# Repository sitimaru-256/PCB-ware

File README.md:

# PCB-ware
"classD_amp" CH224KのVDDとGND間に1uFのキャパシタを追加してください。元の回路のままだと動きません。

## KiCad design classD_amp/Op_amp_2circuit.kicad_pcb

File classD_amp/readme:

CH224KのVDDとGND間に1uFのキャパシタを追加してください。元の回路のままだと動きません。

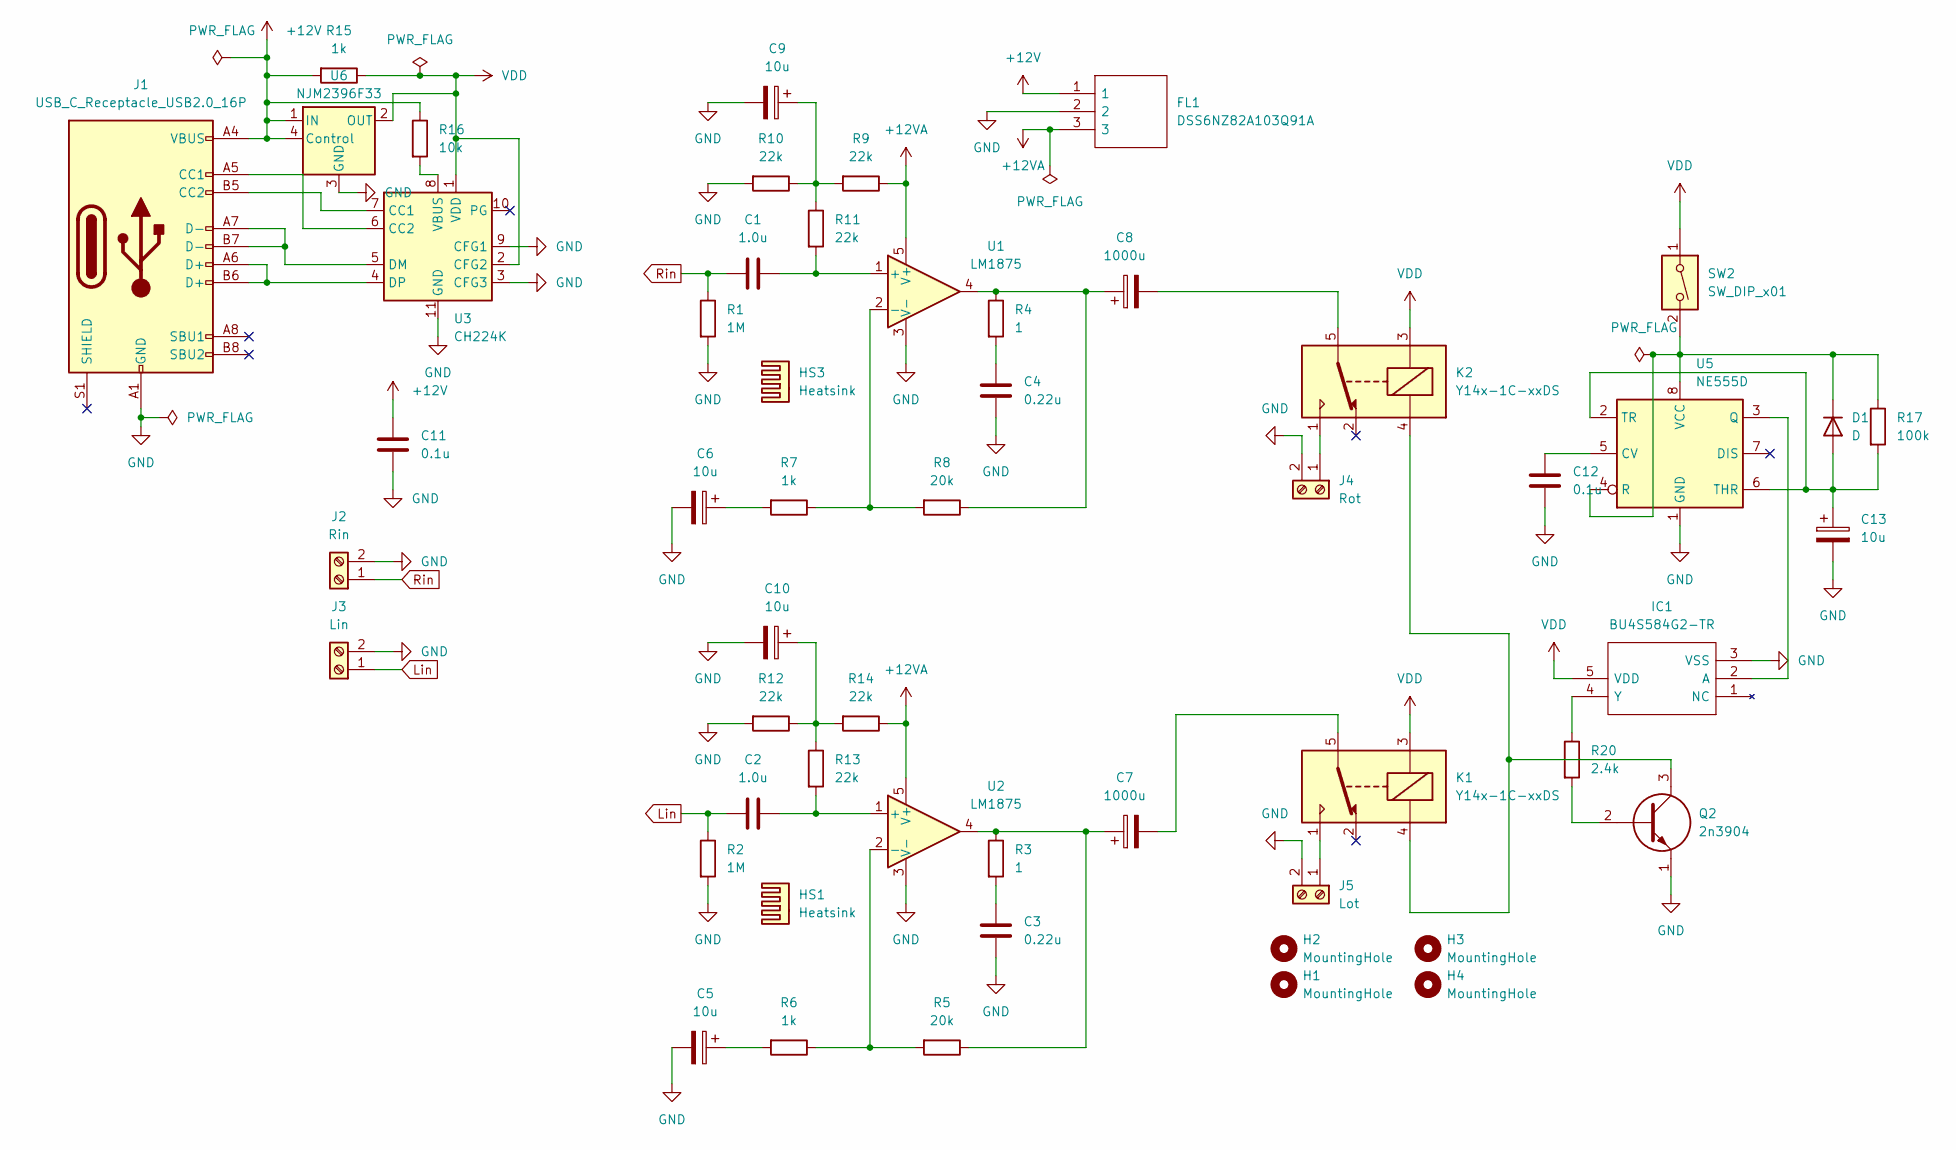
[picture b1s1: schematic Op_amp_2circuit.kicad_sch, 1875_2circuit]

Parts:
C1, C2: 1.0u; C_Rect_L7.0mm_W2.5mm_P5.00mm
C3, C4: 0.22u; C_Rect_L7.0mm_W2.5mm_P5.00mm
C5, C6, C9, C10, C13: 10u; C_Radial_D5.0mm_H11.0mm_P2.00mm
C7, C8: 1000u; C_Radial_D10.0mm_H16.0mm_P5.00mm
C11, C12: 0.1u; C_Rect_L7.0mm_W2.5mm_P5.00mm
D1: D; D_A-405_P7.62mm_Horizontal
FL1: DSS6NZ82A103Q91A; Manufacturer_Part_Number DSS6NZ82A103Q91A
H1, H2, H3, H4: MountingHole; MountingHole_3.2mm_M3
HS1, HS3: Heatsink; Heatsink_54x15x50mm_2xFixationM3
IC1: BU4S584G2-TR; SOT95P280X125-5N; Manufacturer_Part_Number BU4S584G2-TR
J1: USB_C_Receptacle_USB2.0_16P; USB_C_Receptacle_GCT_USB4105-xx-A_16P_TopMnt_Horizontal
J2: Rin; TerminalBlock_Altech_AK300-2_P5.00mm
J3: Lin; TerminalBlock_Altech_AK300-2_P5.00mm
J4: Rot; TerminalBlock_Altech_AK300-2_P5.00mm
J5: Lot; TerminalBlock_Altech_AK300-2_P5.00mm
K1, K2: Y14x-1C-xxDS; 946H-1C-3D
Q2: 2n3904; TS1107A1AP; Manufacturer_Part_Number 2n3904
R1, R2: 1M; R_Axial_DIN0207_L6.3mm_D2.5mm_P7.62mm_Horizontal
R3, R4: 1; R_Axial_DIN0207_L6.3mm_D2.5mm_P7.62mm_Horizontal
R5, R8: 20k; R_Axial_DIN0207_L6.3mm_D2.5mm_P7.62mm_Horizontal
R6, R7, R15: 1k; R_Axial_DIN0207_L6.3mm_D2.5mm_P7.62mm_Horizontal
R9, R10, R11, R12, R13, R14: 22k; R_Axial_DIN0207_L6.3mm_D2.5mm_P7.62mm_Horizontal
R16: 10k; R_Axial_DIN0207_L6.3mm_D2.5mm_P7.62mm_Horizontal
R17: 100k; R_Axial_DIN0207_L6.3mm_D2.5mm_P7.62mm_Horizontal
R20: 2.4k; R_Axial_DIN0207_L6.3mm_D2.5mm_P7.62mm_Horizontal
SW2: SW_DIP_x01; PinHeader_1x02_P2.54mm_Vertical
U1, U2: LM1875; TO-220-5_P3.4x3.7mm_StaggerOdd_Lead3.8mm_Vertical
U3: CH224K; SSOP-10-1EP_3.9x4.9mm_P1mm_EP2.1x3.3mm
U5: NE555D; SOIC-8_3.9x4.9mm_P1.27mm
U6: NJM2396F33; TO-220-4_Vertical

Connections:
+12V: C11.1, FL1.1, J1.A4 (VBUS), J1.A9 (VBUS), J1.B4 (VBUS), J1.B9 (VBUS), R15.2, R16.1, U6.1 (IN), U6.4 (Control)
+12VA: FL1.3, R9.1, R14.1, U1.5 (V+), U2.5 (V+)
GND: C3.1, C4.1, C5.2, C6.2, C9.2, C10.2, C11.2, C12.2, C13.2, FL1.2, IC1.3 (VSS), J1.A1 (GND), J1.A12 (GND), J1.B1 (GND), J1.B12 (GND), J2.2, J3.2, J4.2, J5.2, Q2.1, R1.2, R2.2, R10.2, R12.2, U1.3 (V-), U2.3 (V-), U3.3 (CFG3), U3.9 (CFG1), U3.11 (GND), U5.1 (GND), U6.3 (GND)
Lin: C2.1, J3.1, R2.1
unnamed: C3.2, R3.2
unnamed: C4.2, R4.2
unnamed: C5.1, R6.2
unnamed: C6.1, R7.2
unnamed: C7.1, R3.1, R5.1, U2.4
unnamed: C7.2, K1.5, K1.6
unnamed: C8.1, R4.1, R8.1, U1.4
unnamed: C8.2, K2.5, K2.6
unnamed: C9.1, R9.2, R10.1, R11.1
unnamed: C10.1, R12.1, R13.1, R14.2
unnamed: C13.1, D1.2 (A), R17.2, U5.2 (TR), U5.6 (THR)
unnamed: D1.1 (K), R17.1, SW2.2, U5.4 (R), U5.8 (VCC)
unnamed: IC1.2 (A), U5.3 (Q)
unnamed: IC1.4 (Y), R20.1
unnamed: J1.A5 (CC1), U3.6 (CC2)
unnamed: J1.B5 (CC2), U3.7 (CC1)
unnamed: J4.1, K2.1
unnamed: J5.1, K1.1
unnamed: K1.4, K2.4, Q2.3
unnamed: Q2.2, R20.2
unnamed: C1.2, R11.2, U1.1 (+)
unnamed: R7.1, R8.2, U1.2 (-)
unnamed: C2.2, R13.2, U2.1 (+)
unnamed: R5.2, R6.1, U2.2 (-)
unnamed: J1.A7 (D-), J1.B7 (D-), U3.5 (DM)
unnamed: J1.A6 (D+), J1.B6 (D+), U3.4 (DP)
unnamed: R16.2, U3.8 (VBUS)
unnamed: C12.1, U5.5 (CV)
Rin: C1.1, J2.1, R1.1
VDD: IC1.5 (VDD), K1.3, K2.3, R15.1, SW2.1, U3.1 (VDD), U3.2 (CFG2), U6.2 (OUT)

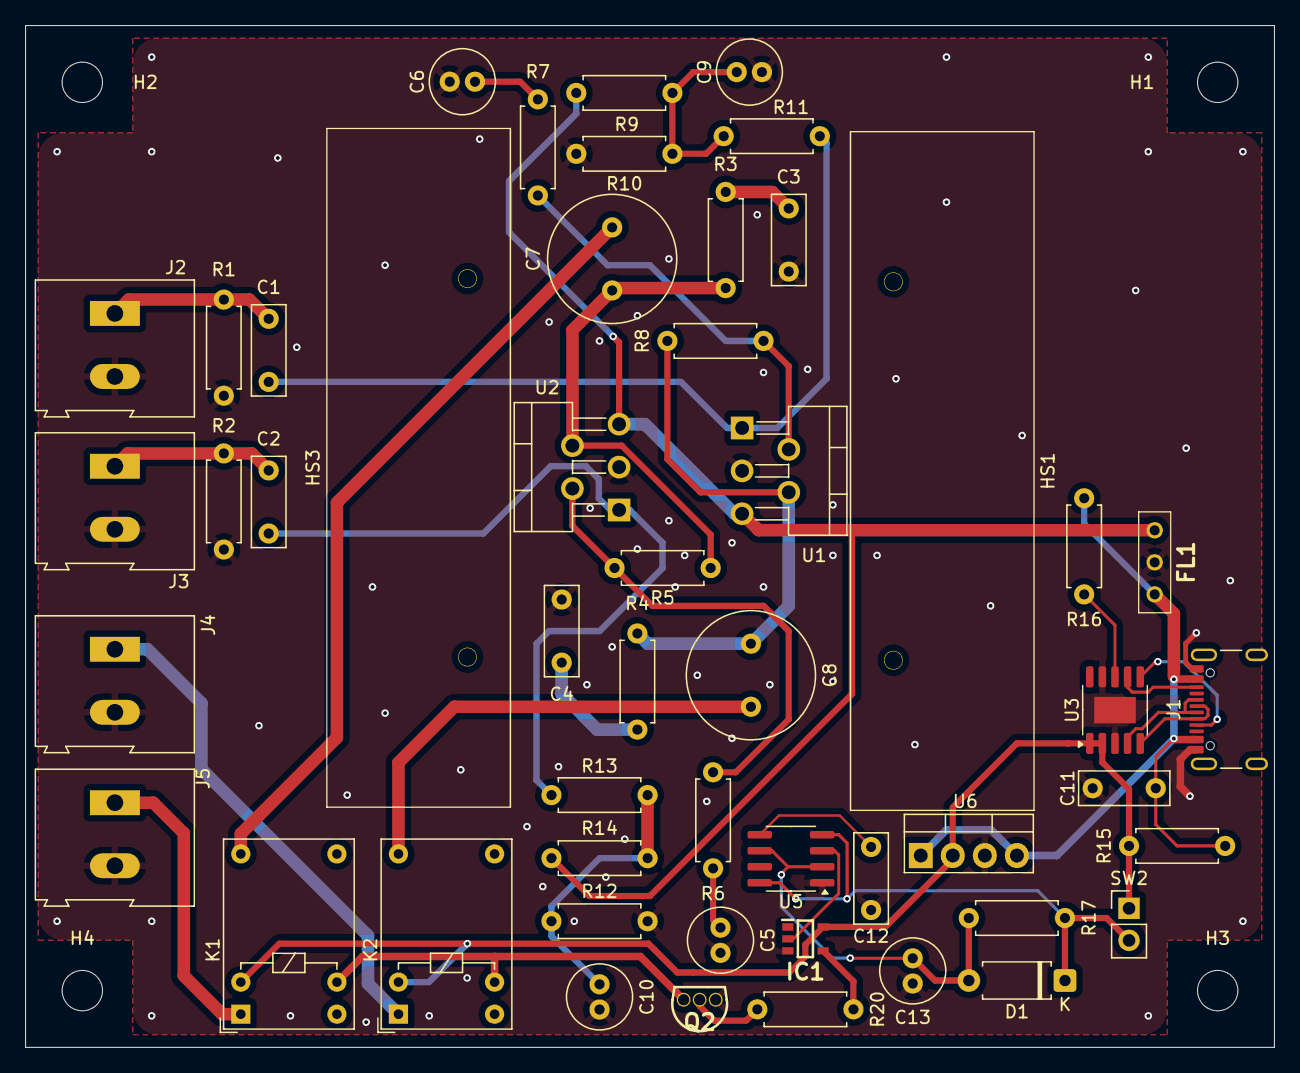
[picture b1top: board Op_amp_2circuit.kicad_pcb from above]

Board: 2 copper layers, 99.0 x 81.0 mm, 54 parts (0 on the bottom side), 34 nets.

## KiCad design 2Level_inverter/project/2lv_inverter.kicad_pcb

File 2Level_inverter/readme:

フォトリレーよりフォトカプラをおすすめします(817系統など)。
電源端子はVHコネクタを想定しています。

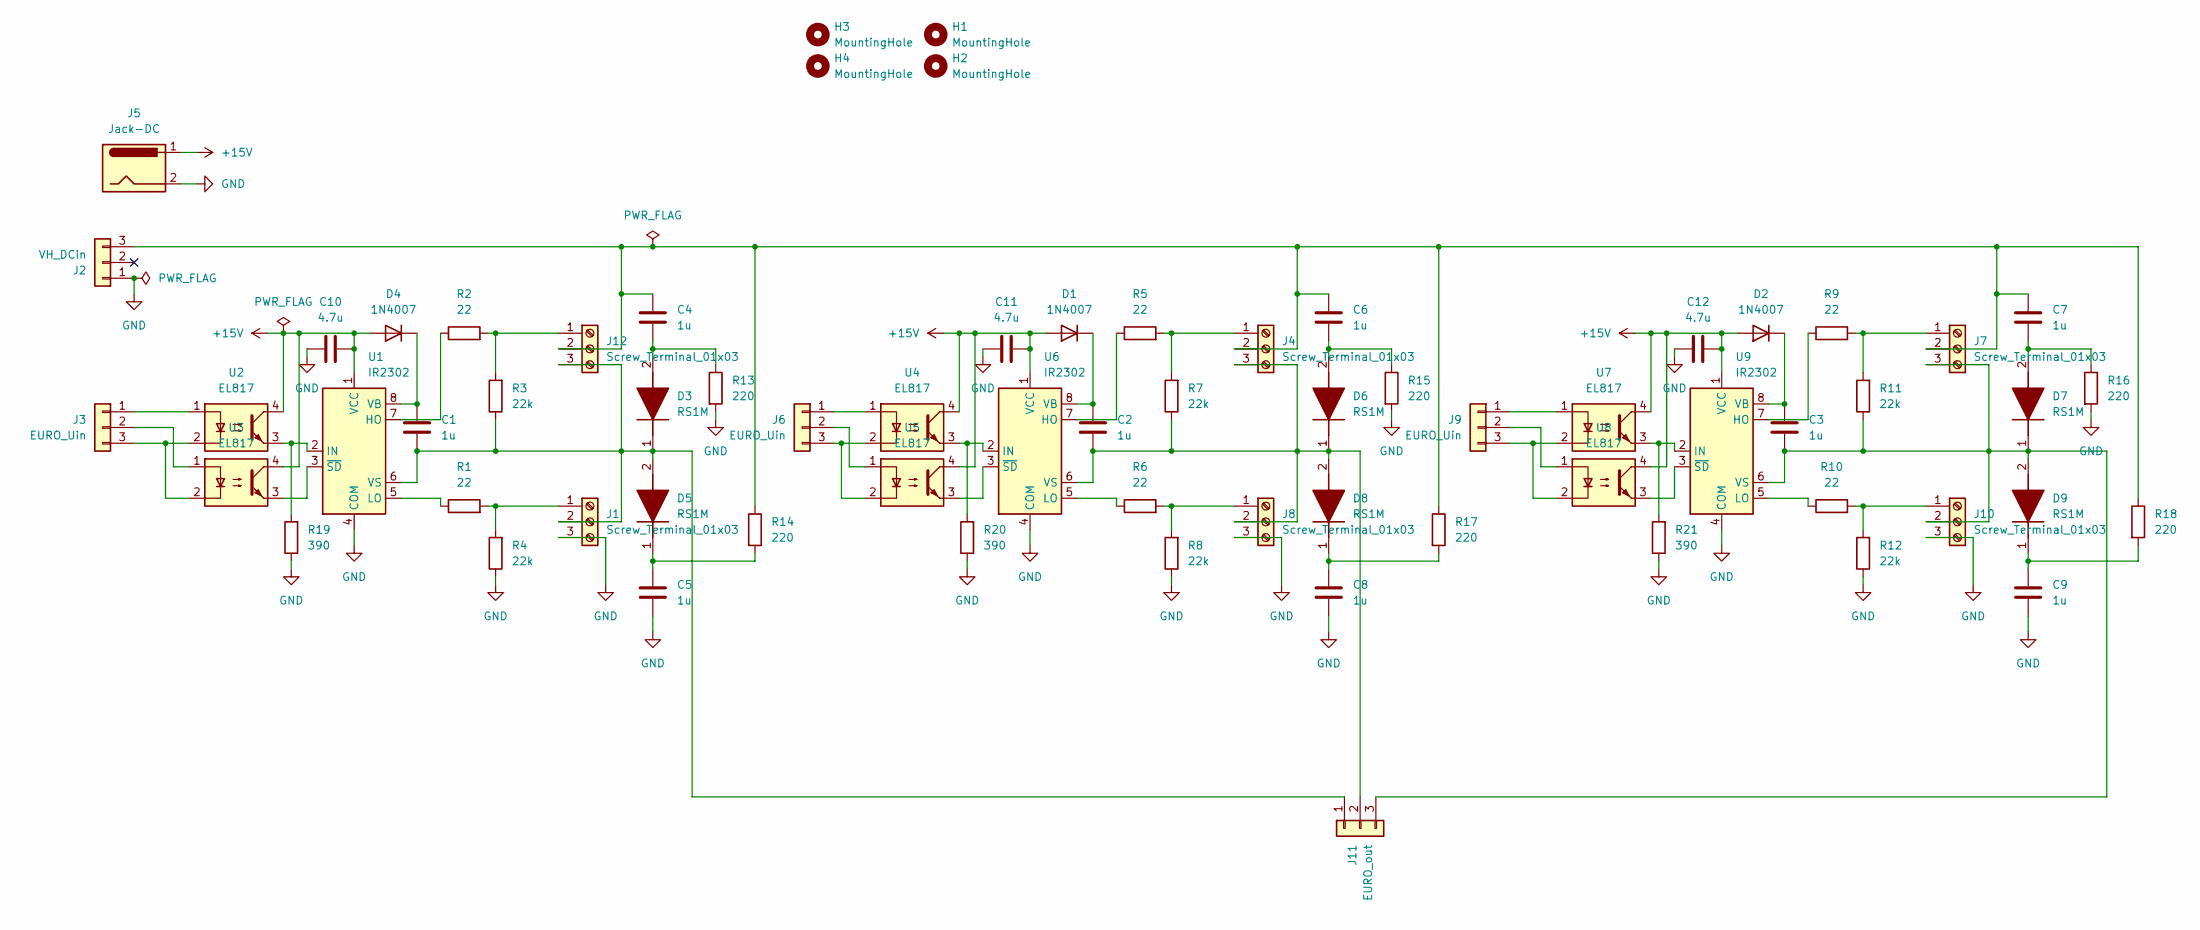
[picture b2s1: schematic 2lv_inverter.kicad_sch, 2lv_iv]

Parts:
C1, C2, C3: 1u; C_Disc_D5.0mm_W2.5mm_P5.00mm
C4, C5, C6, C7, C8, C9: 1u; 630MPS105J
C10, C11, C12: 4.7u; C_Disc_D5.0mm_W2.5mm_P5.00mm
D1, D2, D4: 1N4007; D_DO-41_SOD81_P10.16mm_Horizontal
D3, D5, D6, D7, D8, D9: RS1M; DIOM5126X250N; Manufacturer_Part_Number RS1M
H1, H2, H3, H4: MountingHole; MountingHole_3.2mm_M3
J1, J4, J7, J8, J10, J12: Screw_Terminal_01x03; TB41123E1
J2: VH_DCin; JST_VH_B3P-VH_1x03_P3.96mm_Vertical
J3, J6, J9: EURO_Uin; TerminalBlock_Xinya_XY308-2.54-3P_1x03_P2.54mm_Horizontal
J5: Jack-DC; BarrelJack_Horizontal
J11: EURO_out; TerminalBlock_bornier-3_P5.08mm
R1, R2, R5, R6, R9, R10: 22; R_Axial_DIN0207_L6.3mm_D2.5mm_P7.62mm_Horizontal
R3, R4, R7, R8, R11, R12: 22k; R_Axial_DIN0207_L6.3mm_D2.5mm_P7.62mm_Horizontal
R13, R14, R15, R16, R17, R18: 220; R_Axial_DIN0614_L14.3mm_D5.7mm_P20.32mm_Horizontal
R19, R20, R21: 390; R_Axial_DIN0207_L6.3mm_D2.5mm_P7.62mm_Horizontal
U1, U6, U9: IR2302; SOIC-8_5.3x5.3mm_P1.27mm
U2, U3, U4, U5, U7, U8: EL817; DIP-4_W7.62mm

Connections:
+15V: C10.2, C11.2, C12.2, D1.2 (A), D2.2 (A), D4.2 (A), J5.1, U1.1 (VCC), U2.4, U3.4, U4.4, U5.4, U6.1 (VCC), U7.4, U8.4, U9.1 (VCC)
GND: C5.2, C8.2, C9.2, C10.1, C11.1, C12.1, J1.3, J2.1, J5.2, J8.3, J10.3, R4.1, R8.1, R12.1, R13.2, R15.2, R16.2, R19.1, R20.1, R21.1, U1.4 (COM), U6.4 (COM), U9.4 (COM)
unnamed: C2.1, D1.1 (K), U6.8 (VB)
unnamed: C3.1, D2.1 (K), U9.8 (VB)
unnamed: C4.2, D3.2 (A), R13.1
unnamed: C1.2, D3.1 (K), D5.2 (A), J1.2, J11.1, J12.3, R3.1, U1.6 (VS)
unnamed: C1.1, D4.1 (K), U1.8 (VB)
unnamed: C5.1, D5.1 (K), R14.2
unnamed: C6.2, D6.2 (A), R15.1
unnamed: C2.2, D6.1 (K), D8.2 (A), J4.3, J8.2, J11.2, R7.1, U6.6 (VS)
unnamed: C7.2, D7.2 (A), R16.1
unnamed: C3.2, D7.1 (K), D9.2 (A), J7.3, J10.2, J11.3, R11.1, U9.6 (VS)
unnamed: C8.1, D8.1 (K), R17.2
unnamed: C9.1, D9.1 (K), R18.2
unnamed: J1.1, R1.2, R4.2
unnamed: J3.1, U2.1
unnamed: J3.2, U3.1
unnamed: J3.3, U2.2, U3.2
unnamed: J4.1, R5.2, R7.2
unnamed: J6.1, U4.1
unnamed: J6.2, U5.1
unnamed: J6.3, U4.2, U5.2
unnamed: J7.1, R9.2, R11.2
unnamed: J8.1, R6.2, R8.2
unnamed: J9.1, U7.1
unnamed: J9.2, U8.1
unnamed: J9.3, U7.2, U8.2
unnamed: J10.1, R10.2, R12.2
unnamed: J12.1, R2.2, R3.2
unnamed: C4.1, C6.1, C7.1, J2.3, J4.2, J7.2, J12.2, R14.1, R17.1, R18.1
unnamed: R2.1, U1.7 (HO)
unnamed: R19.2, U1.2 (IN), U2.3
unnamed: R1.1, U1.5 (LO)
unnamed: U1.3 (~SD), U3.3
unnamed: R5.1, U6.7 (HO)
unnamed: R20.2, U4.3, U6.2 (IN)
unnamed: R6.1, U6.5 (LO)
unnamed: U5.3, U6.3 (~SD)
unnamed: R9.1, U9.7 (HO)
unnamed: R21.2, U7.3, U9.2 (IN)
unnamed: R10.1, U9.5 (LO)
unnamed: U8.3, U9.3 (~SD)

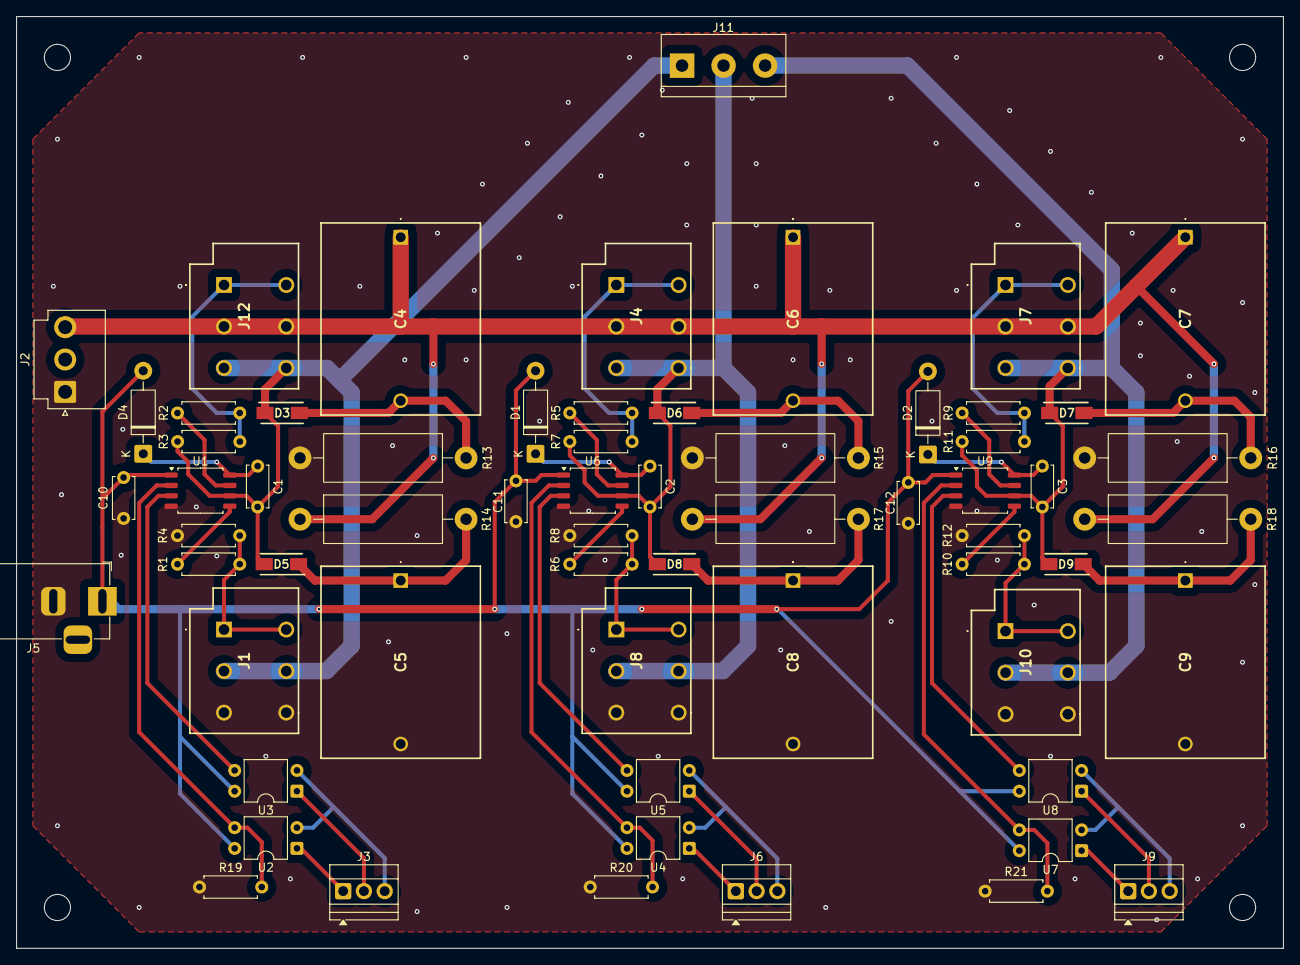
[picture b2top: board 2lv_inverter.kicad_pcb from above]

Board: 2 copper layers, 155.0 x 114.0 mm, 67 parts (0 on the bottom side), 42 nets.
